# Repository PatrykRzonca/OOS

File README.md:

# OOS
OOS - optyczny odbiornik sygnałów

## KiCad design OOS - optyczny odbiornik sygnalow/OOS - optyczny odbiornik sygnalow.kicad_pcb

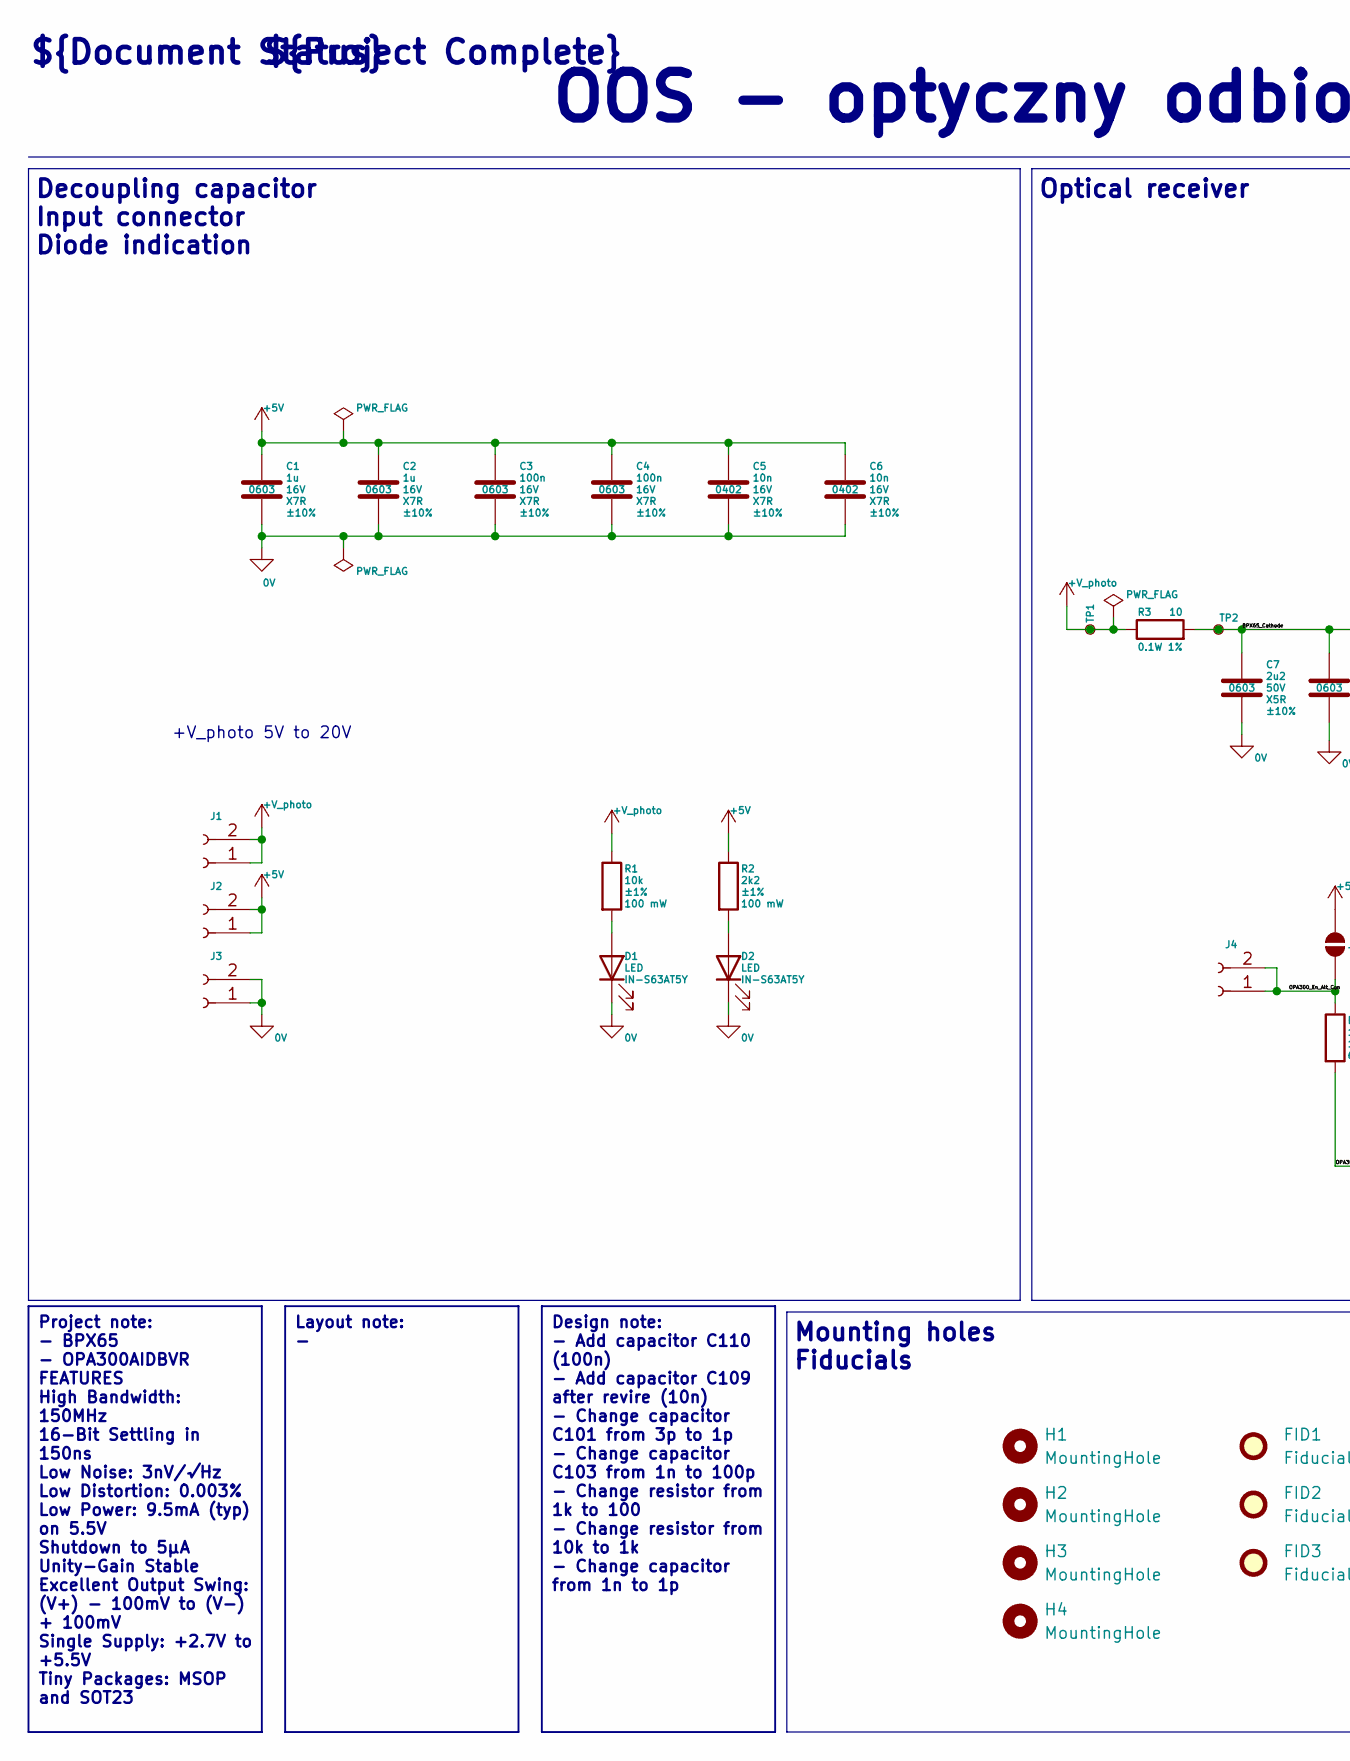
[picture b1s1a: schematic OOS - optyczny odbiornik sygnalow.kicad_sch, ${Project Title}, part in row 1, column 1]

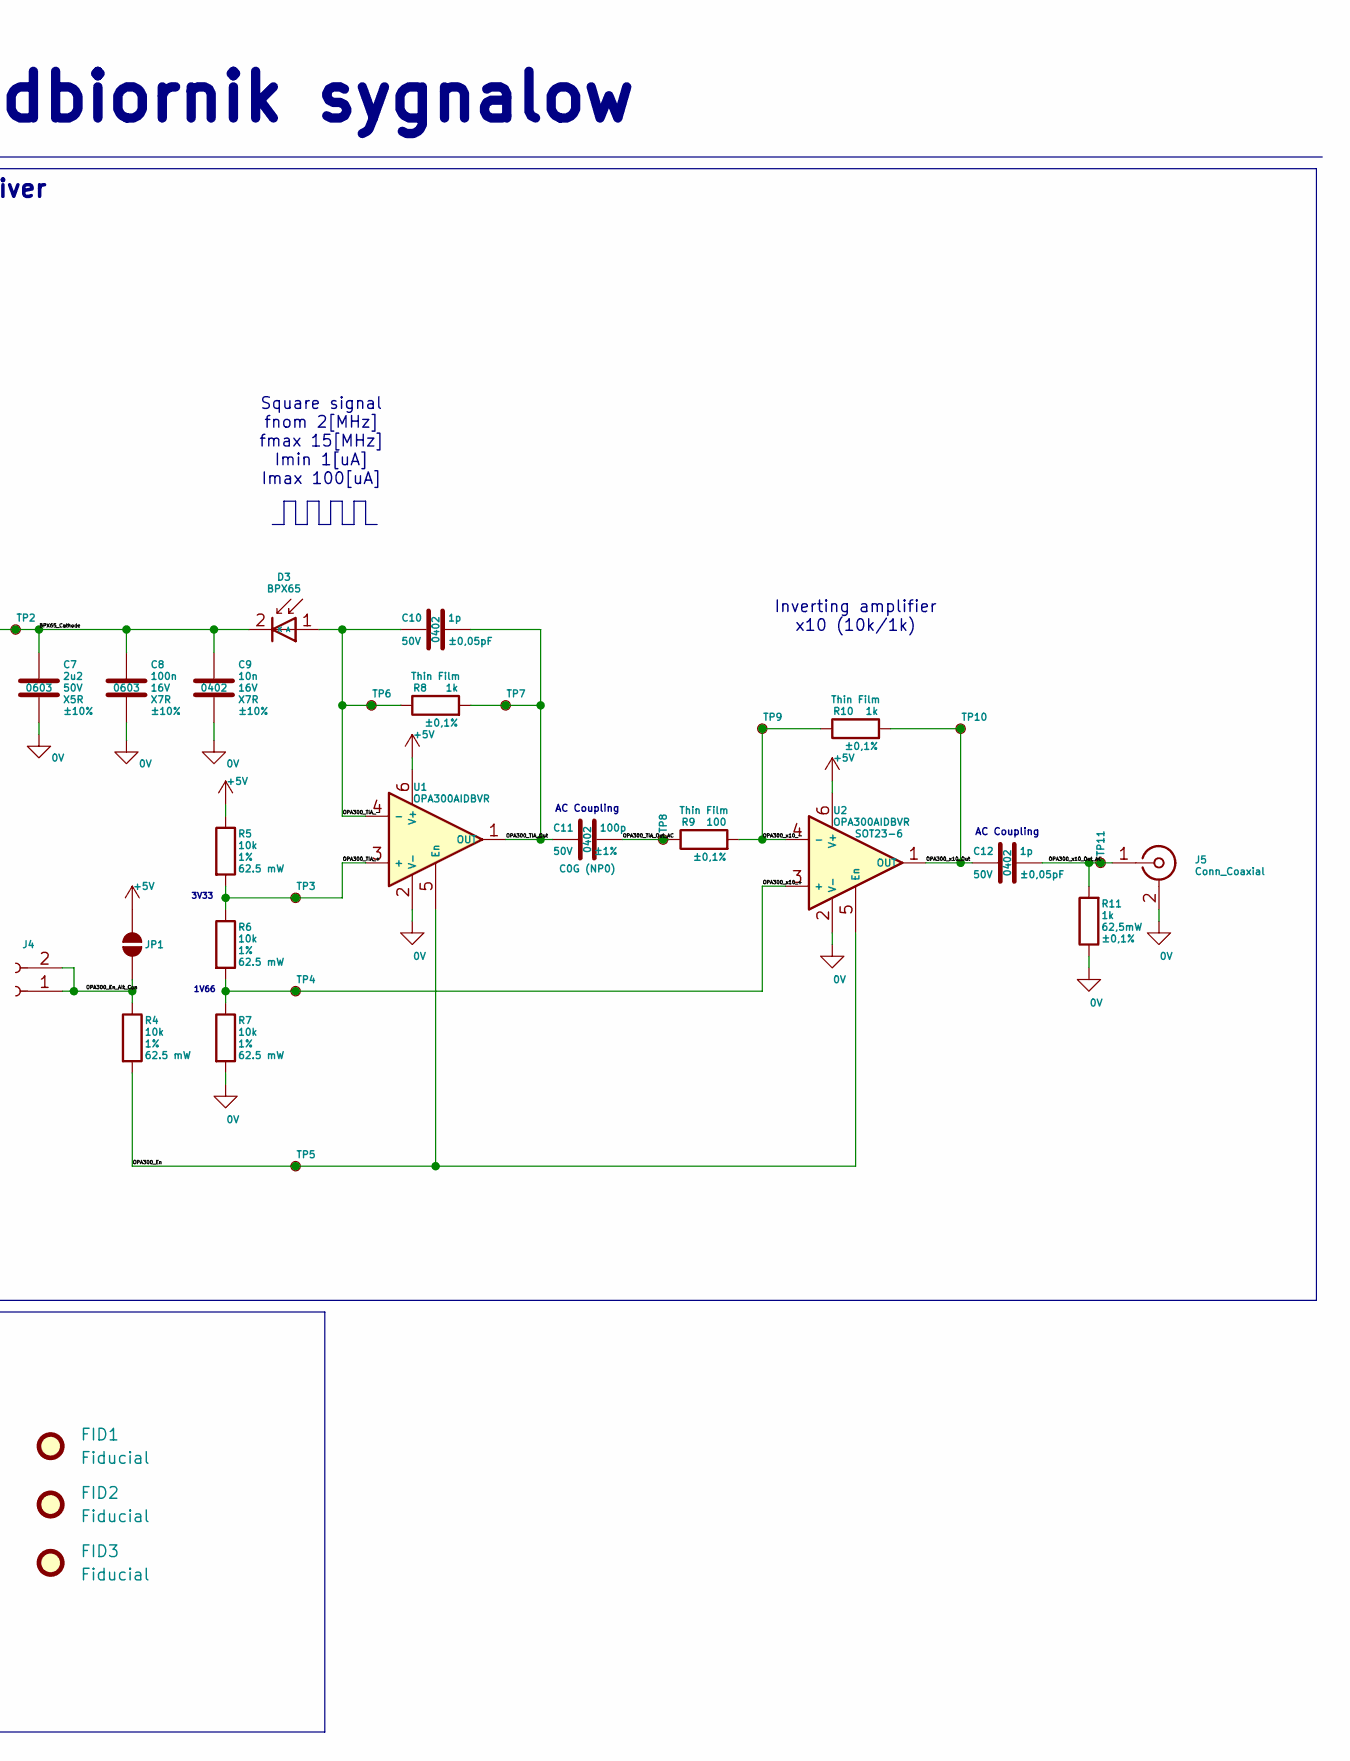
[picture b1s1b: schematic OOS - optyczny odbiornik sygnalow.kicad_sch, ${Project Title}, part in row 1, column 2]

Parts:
C1, C2: 1u; C_0603_1608Metric; Voltage Rating 16V; Tolerance ±10%; MPN after review C0603C105K4RACTU
C3, C4, C8: 100n; C_0603_1608Metric; Voltage Rating 16V; Tolerance ±10%; MPN after review EMK108B7104KA-T
C5, C6, C9: 10n; C_0402_1005Metric; Voltage Rating 16V; Tolerance ±10%; MPN after review CL05B103KO5NNNC
C7: 2u2; C_0603_1608Metric; Voltage Rating 50V; Tolerance ±10%; MPN after review LMK107BJ225KA-T
C10: 1p; C_0402_1005Metric; Voltage Rating 50V; Tolerance ±0,05pF; MPN before review GJM1555C1H3R0WB01D
C11: 100p; C_0402_1005Metric; Voltage Rating 50V; Tolerance ±1%; MPN before review GCM1555C1H102FA16
C12: 1p; C_0402_1005Metric; Voltage Rating 50V; Tolerance ±0,05pF; MPN before review GCM1555C1H102FA16
D1, D2: LED; D_0603_1608Metric; MPN IN-S63AT5Y
D3: BPX65; TO-18-2_Lens
FID1, FID2, FID3: Fiducial; Fiducial_1.5mm_Mask3mm
H1, H2, H3, H4: MountingHole; MountingHole_3.2mm_M3
J1, J2, J3, J4: Conn_01x02_Socket; PinHeader_1x02_P2.54mm_Vertical
J5: Conn_Coaxial; BNC_Amphenol_B6252HB-NPP3G-50_Horizontal
JP1: SolderJumper_2_Open; SolderJumper-2_P1.3mm_Bridged_RoundedPad1.0x1.5mm
R1: 10k; R_0603_1608Metric; Power Rating 100 mW; Tolerance ±1%; MPN RC0603FR-0710KL
R2: 2k2; R_0603_1608Metric; Power Rating 100 mW; Tolerance ±1%; MPN RT0603FRE072K2L
R3: 10; R_0603_1608Metric; Power Rating 0.1W; Tolerance 1%
R4, R5, R6, R7: 10k; R_0402_1005Metric; Power Rating 62.5 mW; Tolerance 1%; MPN after review RC0603JR-13100KL
R8, R11: 1k; R_0402_1005Metric; Power Rating 62,5mW; Tolerance ±0,1%; MPN after review RT0402BRD071KL
R9: 100; R_0402_1005Metric; Power Rating 62,5mW; Tolerance ±0,1%; MPN before review RT0402BRD071KL
R10: 1k; R_0402_1005Metric; Power Rating 62,5mW; Tolerance ±0,1%; MPN before review RT0402BRD0710KL
TP1, TP2, TP3, TP4, TP5, TP6, TP7, TP8, TP9, TP10, TP11: TestPoint_Small; TestPoint_Pad_D1.0mm
U1, U2: OPA300AIDBVR; SOT-23-6_Handsoldering

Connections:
0V: C1.2, C2.2, C3.2, C4.2, C5.2, C6.2, C7.1, C8.2, C9.2, D1.1 (K), D2.1 (K), J3.1, J3.2, J5.2 (Ext), R7.2, R11.1, U1.2 (V-), U2.2 (V-)
+5V: C1.1, C2.1, C3.1, C4.1, C5.1, C6.1, J2.1, J2.2, JP1.2 (B), R2.1, R5.1, U1.6 (V+), U2.6 (V+)
+V_photo: J1.1, J1.2, R1.1, R3.1, TP1.1
/BPX65_Cathode: C7.2, C8.1, C9.1, D3.2 (K), R3.2, TP2.1
/OPA300_En: R4.2, TP5.1, U1.5 (En), U2.5 (En)
/OPA300_En_Alt_Con: J4.1, J4.2, JP1.1 (A), R4.1
/OPA300_TIA_+: R5.2, R6.1, TP3.1, U1.3 (+)
/OPA300_TIA_-: C10.1, D3.1 (A), R8.1, TP6.1, U1.4 (-)
/OPA300_TIA_Out: C10.2, C11.1, R8.2, TP7.1, U1.1 (OUT)
/OPA300_TIA_Out_AC: C11.2, R9.1, TP8.1
/OPA300_x10_+: R6.2, R7.1, TP4.1, U2.3 (+)
/OPA300_x10_-: R9.2, R10.1, TP9.1, U2.4 (-)
/OPA300_x10_Out: C12.1, R10.2, TP10.1, U2.1 (OUT)
/OPA300_x10_Out_AC: C12.2, J5.1 (In), R11.2, TP11.1
unnamed: D1.2 (A), R1.2
unnamed: D2.2 (A), R2.2

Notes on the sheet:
+V_photo 5V to 20V
1V66
${Document Status}
Mounting holes Fiducials
Decoupling capacitor Input connector Diode indication
Optical receiver
${Project Complete}
AC Coupling
Square signal fnom 2[MHz] fmax 15[MHz] Imin 1[uA] Imax 100[uA]
OOS - optyczny odbiornik sygnalow
Inverting amplifier x10 (10k/1k)
3V33
Design note: - Add capacitor C110 (100n) - Add capacitor C109 after revire (10n) - Change capacitor C101 from 3p to 1p - Change capacitor C103 from 1n to 100p - Change resistor from 1k to 100 - Change resistor from 10k to 1k - Change capacitor from 1n to 1p
Layout note: -
Project note: - BPX65 - OPA300AIDBVR FEATURES High Bandwidth: 150MHz 16-Bit Settling in 150ns Low Noise: 3nV/√Hz Low Distortion: 0.003% Low Power: 9.5mA (typ) on 5.5V Shutdown to 5μA Unity-Gain Stable Excellent Output Swing: (V+) − 100mV to (V−) + 100mV Single Supply: +2.7V to +5.5V Tiny Packages: 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

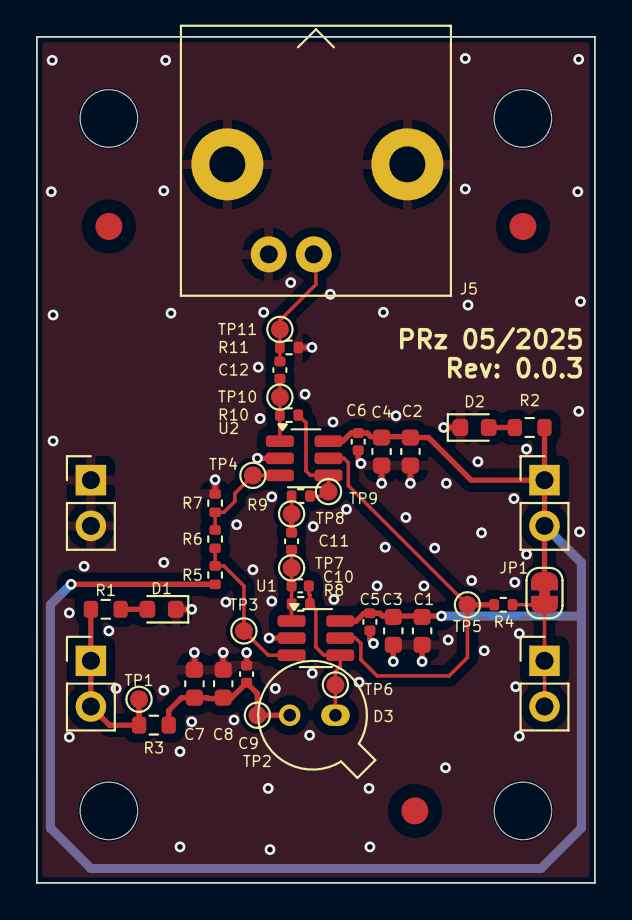
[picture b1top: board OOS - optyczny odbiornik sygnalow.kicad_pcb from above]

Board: 2 copper layers, 31.0 x 47.0 mm, 52 parts (0 on the bottom side), 16 nets.

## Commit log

2025-04-26 Budowa schematu, ponad połowa skończona
2025-04-26 Dodanie zlacz na +V_photo, +5V i 0V
2025-04-26 Dodanie zasilania i rezystora do pinu enable
2025-04-26 Dodane kondensatory odsprzegajace, poukladane informacje dla kazdego elementu zasilania
2025-04-26 Schemat po review z AI, wpisane co potrzeba zmienic
2025-04-26 Dodanie dalszych komentarzy po przegladzie
2025-04-27 Przesuniecie komentarza
2025-04-27 Poprawa na schemacie, dodanie otworów i pozycjonerow, wczytanie komponentow na pcb
2025-04-27 Polozenei komponentow na plycie, zdefiniowanie geometri, wczesny layout
2025-04-27 Wstepne polaczenie komponentow, ustawienie plaszczyzny masy, ustalenie 2 warstw plytki
2025-04-30 Polozenie komponentow, layout w wersji 0.0
2025-05-02 Wysprzątanie schematu, ustalenie statusu Released i wykończenia 100%
2025-05-03 Uwidocznienie reszty komponentow, dodanie klas sieci, poprawa wizualna
2025-05-03 Wpisanie wersji v0.0.1 do projektu na schemacie
2025-05-03 Dodanie dokumentu z ulepszeniami dla dalszych wersji
2025-05-04 Dodanie wielkosci obudow do reszty kompoenntow, poprawienie polozenia parametrow dla komponentow
2025-05-07 Wyczyszczenie schematu i PCB (Ustalenie wymiarowania, Charakterystyki PCB)
2025-05-08 Rozdzielenie projektu na strony, analogowa, ladowanie, usb, boost
2025-05-09 Sekcja_DCDC_Boost - gotowa v1.0 schematu. Komponenty maja dodane MPN, linki do datasheetow, zakladek na stronie TME i kluczowe parametry. Dodano opisy Layout notes, Design notes i Project Note w styl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
2025-05-13 Add review notes for DCDC_Boost page
2025-05-15 Dodane test pointy i net labels. Napiecie wyjsciowe zmienione z 20V na 31.82V (rezystory w FB zmienione). Zmieniona dioda D4 na 60V br, 0.5V forward, 2A. Dodany Jumper na Shutdown pin U3. Dodane 0R n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
2025-05-16 Przeniesienie zmian z brancha Filip na review ze schematu Sekcja_DCDC_Boost
2025-05-16 Review Sekcja_Analogowa
2025-05-21 Solved points from review on page OOS - Analog
